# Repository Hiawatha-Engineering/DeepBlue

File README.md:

# Phone Model DeepBlue

A Pi hat to enable use of a Raspberry Pi as a phone.

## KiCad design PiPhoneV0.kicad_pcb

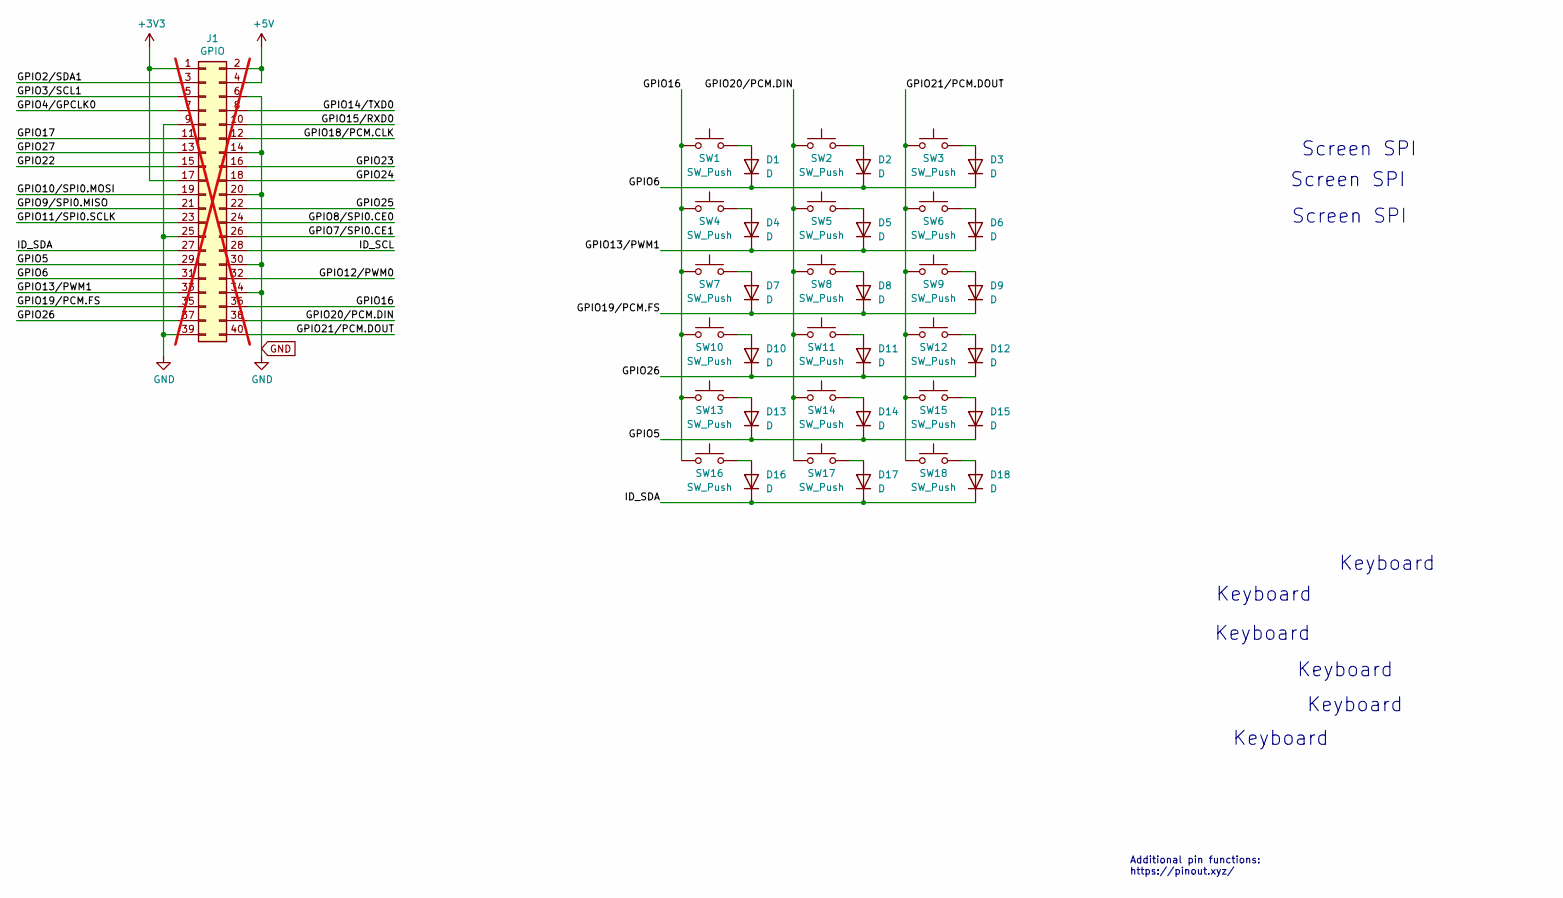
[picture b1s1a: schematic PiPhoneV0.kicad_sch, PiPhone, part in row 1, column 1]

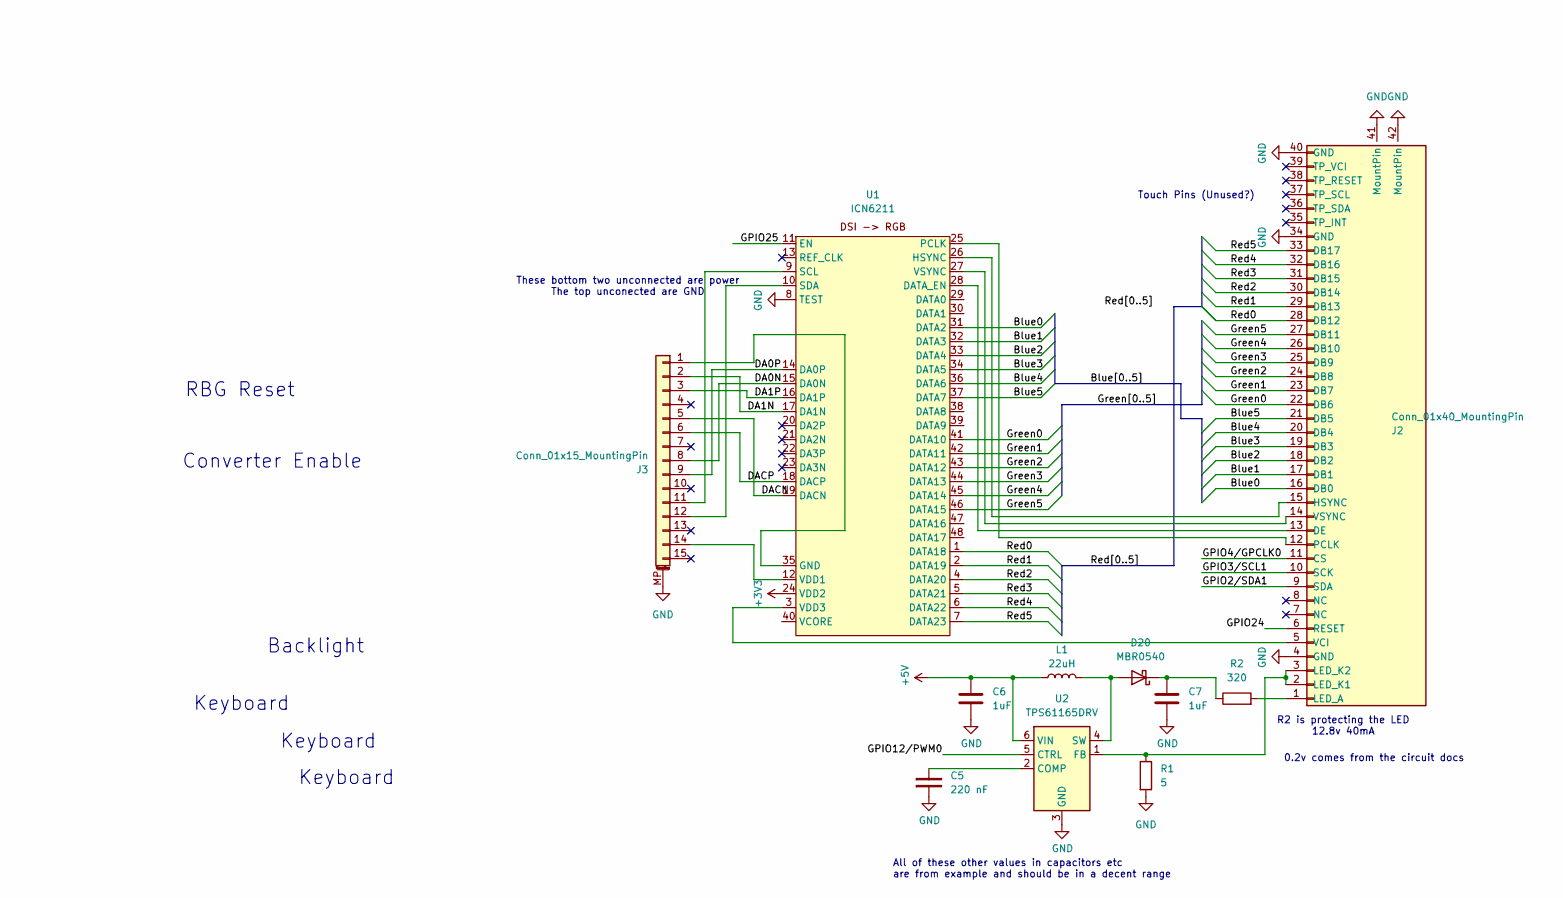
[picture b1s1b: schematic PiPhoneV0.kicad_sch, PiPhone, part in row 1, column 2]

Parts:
C5: 220 nF; C_0201_0603Metric; LCSC Part # C21120
C6, C7: 1uF; C_0201_0603Metric; LCSC Part # C15849
D1, D2, D3, D4, D5, D6, D7, D8, D9, D10, D11, D12, D13, D14, D15, D16, D17, D18: D; D_SOD-323; LCSC Part # C2128
D20: MBR0540; D_SOD-123; LCSC Part # C77337
J1: GPIO; PinSocket_2x20_P2.54mm_Vertical; not fitted
J2: Conn_01x40_MountingPin; CONN-SMD_40P-P0.50_HCTL_HC-FPC-05-09-40RLTAG; LCSC Part # C5213762
J3: Conn_01x15_MountingPin; FPC-SMD_15P-P1.00_HDGC_1.0K-GT-15PB; LCSC Part # C2915527
L1: 22uH; IND-SMD_L5.0-W5.0-P3.60_SMNR5040; LCSC Part # C9391
R1: 5; R_0201_0603Metric; LCSC Part # C6145550
R2: 320; R_0201_0603Metric; LCSC Part # C863039
SW1, SW2, SW3, SW4, SW5, SW6, SW7, SW8, SW9, SW10, SW11, SW12, SW13, SW14, SW15, SW16, SW17, SW18: SW_Push; SW_Gateron_LowProfile_THT
U1: ICN6211; QFN-48_L6.0-W6.0-P0.40-TL-EP4.2; LCSC Part # C246085
U2: TPS61165DRV; WSON-6-1EP_2x2mm_P0.65mm_EP1x1.6mm; LCSC Part # C122568

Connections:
+3V3: J1.1, J1.17, U1.24 (VDD2)
+5V: C6.2, J1.2, J1.4, L1.1, U2.6 (VIN)
/Blue0: J2.16 (DB0), U1.31 (DATA2)
/Blue1: J2.17 (DB1), U1.32 (DATA3)
/Blue2: J2.18 (DB2), U1.33 (DATA4)
/Blue3: J2.19 (DB3), U1.34 (DATA5)
/Blue4: J2.20 (DB4), U1.36 (DATA6)
/Blue5: J2.21 (DB5), U1.37 (DATA7)
/DA0N: J3.8, U1.15 (DA0N)
/DA0P: J3.9, U1.14 (DA0P)
/DA1N: J3.2, U1.17 (DA1N)
/DA1P: J3.3, U1.16 (DA1P)
/DACN: J3.5, U1.19 (DACN)
/DACP: J3.6, U1.18 (DACP)
/GPIO2/SDA1: J1.3, J2.9 (SDA)
/GPIO3/SCL1: J1.5, J2.10 (SCK)
/GPIO4/GPCLK0: J1.7, J2.11 (CS)
/GPIO5: D13.1 (K), D14.1 (K), D15.1 (K), J1.29
/GPIO6: D1.1 (K), D2.1 (K), D3.1 (K), J1.31
/GPIO7/SPI0.CE1: J1.26
/GPIO8/SPI0.CE0: J1.24
/GPIO9/SPI0.MISO: J1.21
/GPIO10/SPI0.MOSI: J1.19
/GPIO11/SPI0.SCLK: J1.23
/GPIO12/PWM0: J1.32, U2.5 (CTRL)
/GPIO13/PWM1: D4.1 (K), D5.1 (K), D6.1 (K), J1.33
/GPIO14/TXD0: J1.8
/GPIO15/RXD0: J1.10
/GPIO16: J1.36, SW1.1, SW4.1, SW7.1, SW10.1, SW13.1, SW16.1
/GPIO17: J1.11
/GPIO18/PCM.CLK: J1.12
/GPIO19/PCM.FS: D7.1 (K), D8.1 (K), D9.1 (K), J1.35
/GPIO20/PCM.DIN: J1.38, SW2.1, SW5.1, SW8.1, SW11.1, SW14.1, SW17.1
/GPIO21/PCM.DOUT: J1.40, SW3.1, SW6.1, SW9.1, SW12.1, SW15.1, SW18.1
/GPIO22: J1.15
/GPIO23: J1.16
/GPIO24: J1.18, J2.6 (RESET)
/GPIO25: J1.22, U1.11 (EN)
/GPIO26: D10.1 (K), D11.1 (K), D12.1 (K), J1.37
/GPIO27: J1.13
/Green0: J2.22 (DB6), U1.41 (DATA10)
/Green1: J2.23 (DB7), U1.42 (DATA11)
/Green2: J2.24 (DB8), U1.43 (DATA12)
/Green3: J2.25 (DB9), U1.44 (DATA13)
/Green4: J2.26 (DB10), U1.45 (DATA14)
/Green5: J2.27 (DB11), U1.46 (DATA15)
/ID_SCL: J1.28
/ID_SDA: D16.1 (K), D17.1 (K), D18.1 (K), J1.27
/Red0: J2.28 (DB12), U1.1 (DATA18)
/Red1: J2.29 (DB13), U1.2 (DATA19)
/Red2: J2.30 (DB14), U1.4 (DATA20)
/Red3: J2.31 (DB15), U1.5 (DATA21)
/Red4: J2.32 (DB16), U1.6 (DATA22)
/Red5: J2.33 (DB17), U1.7 (DATA23)
GND: C5.1, C6.1, C7.1, J1.6, J1.9, J1.14, J1.20, J1.25, J1.30, J1.34, J1.39, J2.4 (GND), J2.34 (GND), J2.40 (GND), J2.41 (MountPin), J2.42 (MountPin), J3.MP (MountPin), R1.2, U1.8 (TEST), U2.3 (GND), U2.7 (GND)
unnamed: D1.2 (A), SW1.2
unnamed: D2.2 (A), SW2.2
unnamed: D3.2 (A), SW3.2
unnamed: D4.2 (A), SW4.2
unnamed: D5.2 (A), SW5.2
unnamed: D6.2 (A), SW6.2
unnamed: D7.2 (A), SW7.2
unnamed: D8.2 (A), SW8.2
unnamed: D9.2 (A), SW9.2
unnamed: D10.2 (A), SW10.2
unnamed: D11.2 (A), SW11.2
unnamed: D12.2 (A), SW12.2
unnamed: D13.2 (A), SW13.2
unnamed: D14.2 (A), SW14.2
unnamed: D15.2 (A), SW15.2
unnamed: D16.2 (A), SW16.2
unnamed: D17.2 (A), SW17.2
unnamed: D18.2 (A), SW18.2
unnamed: D20.2 (A), L1.2, U2.4 (SW)
unnamed: C7.2, D20.1 (K), R2.1
unnamed: J2.13 (DE), U1.28 (DATA_EN)
unnamed: J2.15 (HSYNC), U1.26 (HSYNC)
unnamed: J2.1 (LED_A), R2.2
unnamed: J2.2 (LED_K1), J2.3 (LED_K2), R1.1, U2.1 (FB)
unnamed: J2.12 (PCLK), U1.25 (PCLK)
unnamed: J2.5 (VCI), U1.3 (VDD3)
unnamed: J2.14 (VSYNC), U1.27 (VSYNC)
unnamed: J3.1, U1.35 (GND)
unnamed: J3.11, U1.9 (SCL)
unnamed: J3.12, U1.10 (SDA)
unnamed: J3.14, U1.12 (VDD1)
unnamed: C5.2, U2.2 (COMP)

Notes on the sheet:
Keyboard
Additional pin functions: https://pinout.xyz/
Screen SPI
Converter Enable
RBG Reset
These bottom two unconnected are power The top unconected are GND
Touch Pins (Unused?)
R2 is protecting the LED 12.8v 40mA
Backlight
All of these other values in capacitors etc are from example and should be in a decent range
0.2v comes from the circuit docs

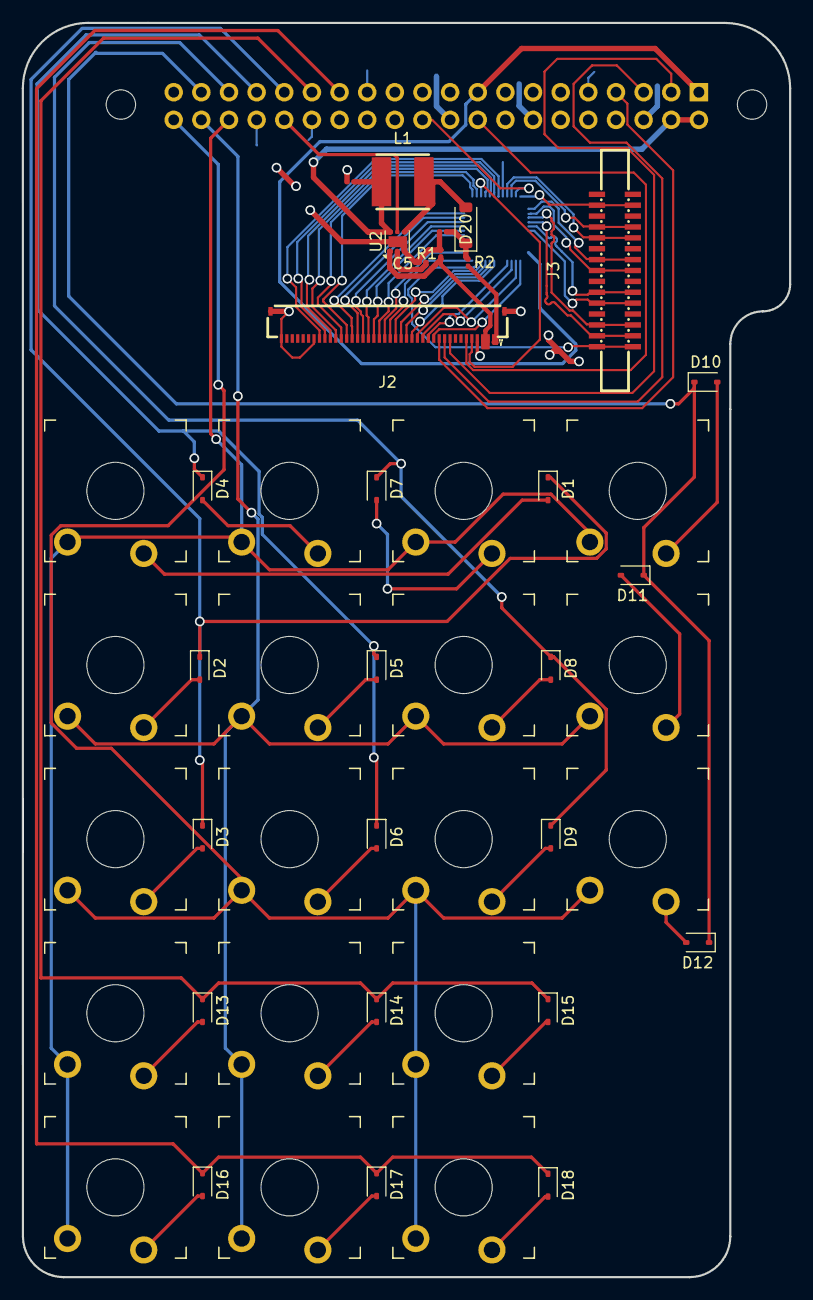
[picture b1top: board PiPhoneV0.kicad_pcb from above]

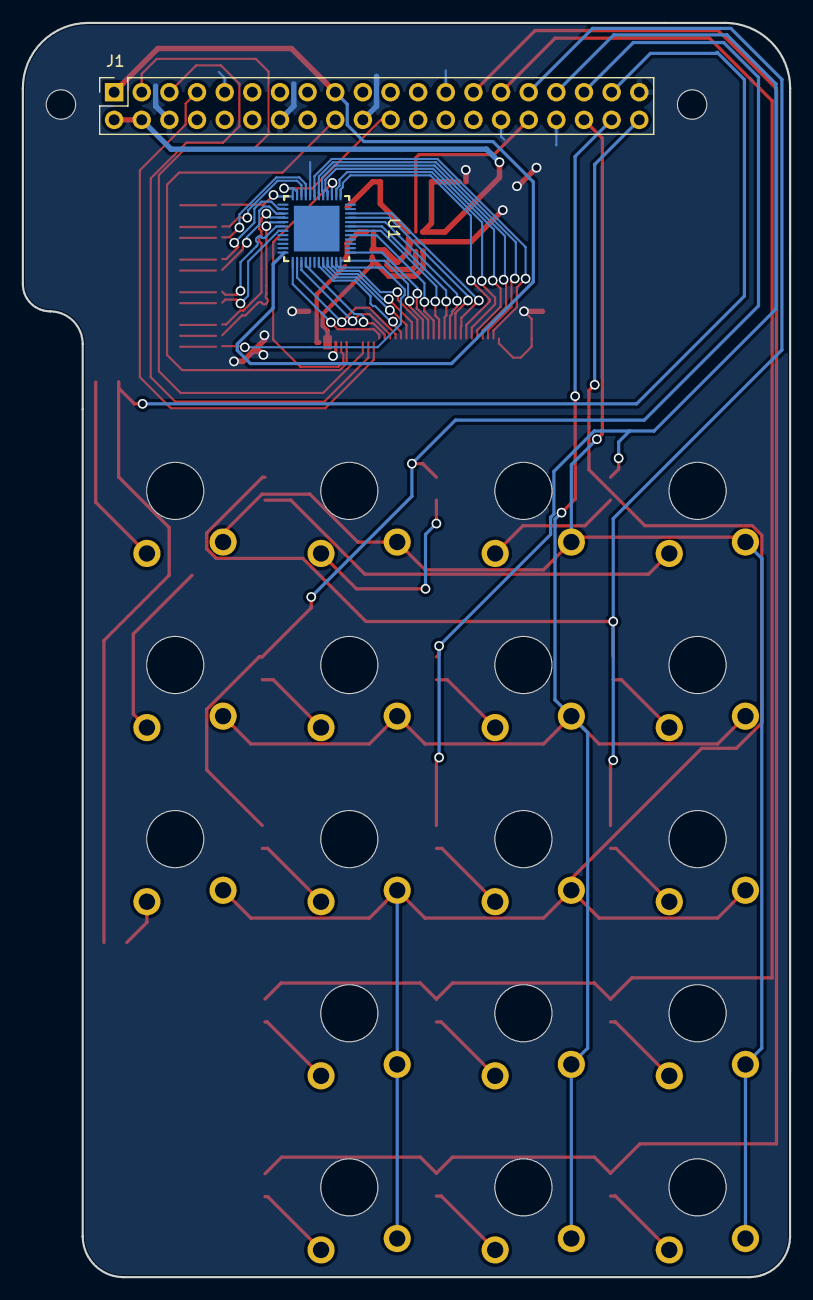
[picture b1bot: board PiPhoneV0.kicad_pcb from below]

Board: 2 copper layers, 70.5 x 115.3 mm, 50 parts (2 on the bottom side), 74 nets.

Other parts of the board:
MH3, MH4: MountingHole_2.7mm_M2.5

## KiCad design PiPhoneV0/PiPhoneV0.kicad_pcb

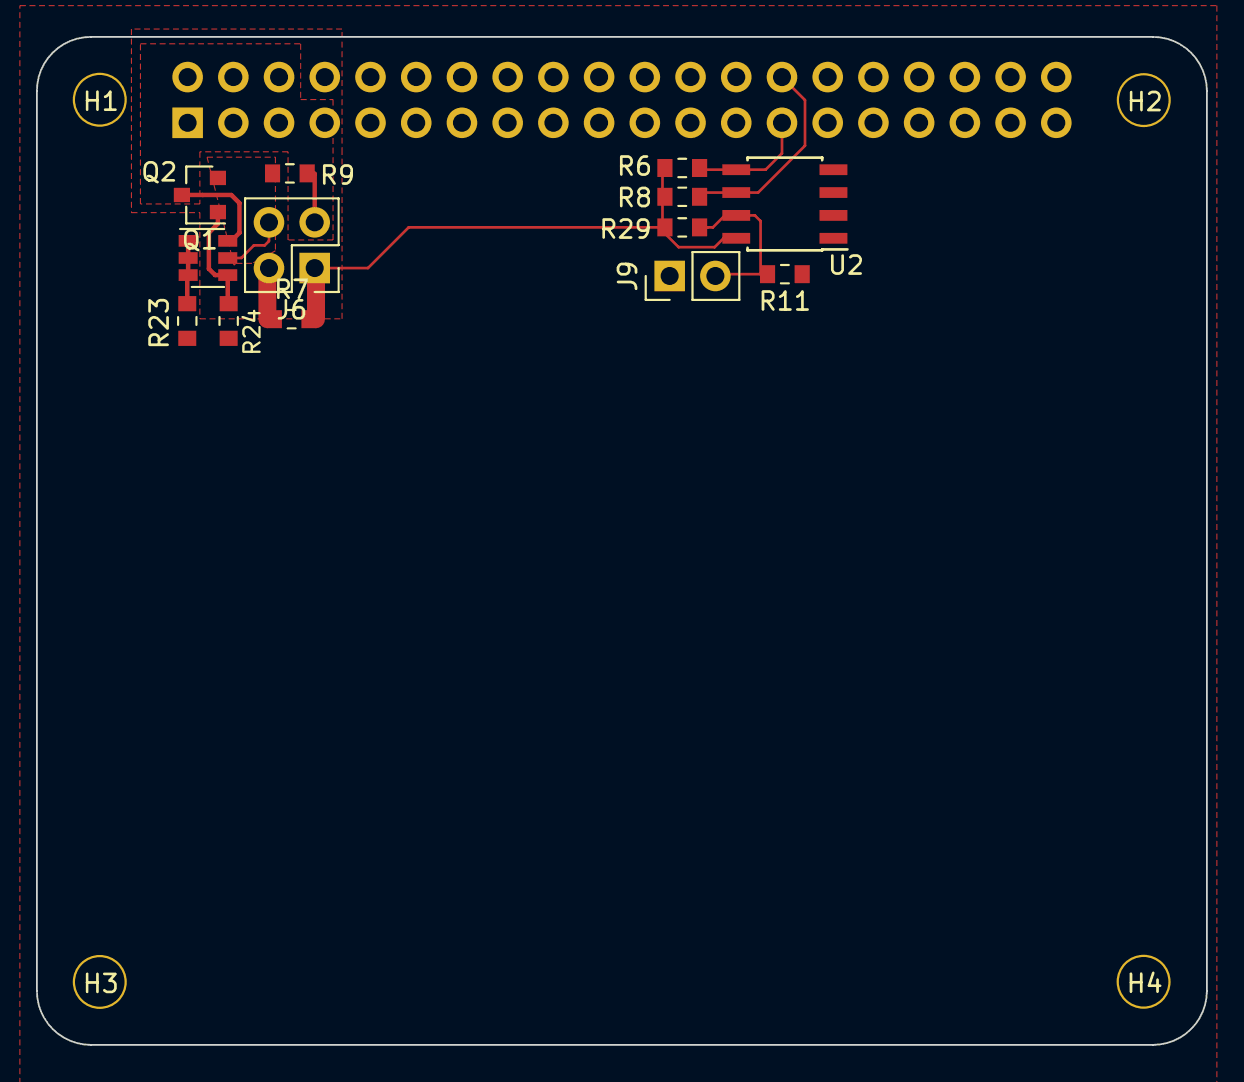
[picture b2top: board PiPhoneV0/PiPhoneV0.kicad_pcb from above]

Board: 4 copper layers, 65.0 x 56.0 mm, 18 parts (1 on the bottom side), 10 nets.

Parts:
H1, H2, H3, H4: 3mm_Mounting_Hole; NPTH_3mm_ID
J3: 40HAT; PinSocket_2x20_P2.54mm_Vertical
J6: CONN_02X02; PinHeader_2x02_P2.54mm_Vertical
J9: CONN_01X02; PinHeader_1x02_P2.54mm_Vertical
Q1: DMG2305UX; SOT-23
Q2: DMMT5401; SOT-23-6
R6, R8: 3.9K; R_0603_1608Metric_Pad0.84x1.00mm_HandSolder
R7, R9, R11: DNP; R_0603_1608Metric_Pad0.84x1.00mm_HandSolder
R23, R29: 10K; R_0603_1608Metric_Pad0.84x1.00mm_HandSolder
R24: 47K; R_0603_1608Metric_Pad0.84x1.00mm_HandSolder
U2: CAT24C32; SOIC-8_3.9x4.9mm_P1.27mm

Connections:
/ID_SC_EEPROM: J3.28 (BCM1), R8.2, U2.6 (SCL)
/ID_SD_EEPROM: J3.27 (BCM0), R6.2, U2.5 (SDA)
/P3V3: J6.1, R6.1, R7.2, R8.1, R29.1, U2.8 (VCC)
/P3V3_HAT: J3.1 (P3V3), J6.2, R7.1
/P5V: J6.3, Q1.3 (D), Q2.6 (E), R9.2
/P5V_HAT: J3.2 (P5V), J3.4 (P5V), J6.4, Q1.2 (S), Q2.5 (E), R9.1
GND: J3.6 (GND), J3.9 (GND), J3.14 (GND), J3.20 (GND), J3.25 (GND), J3.30 (GND), J3.34 (GND), J3.39 (GND), J9.1, R11.2, R23.2, R24.2, U2.1 (A0), U2.2 (A1), U2.3 (A2), U2.4 (GND)
unnamed: J9.2, R11.1, R29.2, U2.7 (WP)
unnamed: Q1.1 (G), Q2.4 (C), R24.1
unnamed: Q2.1 (C), Q2.2 (B), Q2.3 (B), R23.1

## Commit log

2025-06-01 init
2025-06-10 fix: remove lock file
2025-06-21 feat: speaker
2025-06-21 chore: clean up git repo, properly ignore cache files
2025-06-26 chore: flip pcb
2025-07-22 chore: body curve
2025-07-31 fix: switch key switches for low profile
2025-08-05 feat: routing
2025-08-21 wip: backlight
2025-08-22 feat: screen
2025-08-22 doc: document resistor values
2025-08-22 feat: protect backlight led
2025-08-22 docs: protect backlight led note
2025-08-22 fix: move up bottom of the pcb
2025-08-26 chore: add journal
2025-08-27 feat: add ground plane, clean up keyboard wiring, move around connectors.
    Note: still need to do length tuning on differential pairs and make sure
    rgb signal will work ok in its current configuration.
2025-08-27 chore: journal image
2025-08-29 chore: tune length of diferential pairs
2025-08-29 chore: generate gerbers
2025-08-30 chore: match components with jlpcb
2025-08-30 chore: match parts with jlpcb
2025-10-08 feat: update adapters to match those easily on jlpcb
2025-10-16 chore: chill out drc a bit more
2025-10-17 feat: 3d models for everything!
